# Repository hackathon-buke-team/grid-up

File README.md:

# PANO GÖZ / Son 7 takım arasına kalındı. Nihai sıralama açıklanmadı.

**Pano/hücre içi anomali erken uyarı sistemi — ADM & GDZ Elektrik "Grid Up" Hackathon**

Varlık: TEDAŞ-MLZ/2003-06.B, EK-II/14 çizimli, 1600 kVA dahili tip AG dağıtım panosu.
1600×1500×450 mm, 2312 A ana bara, 38 kA rms / 80 kA tepe kısa devre, IP2X, Form 2B.

---

## 1. Tez — bir paragrafta

Her yarışmacı panoya bir termometre koyar ve bir eşiğin üstünde alarm üretir. Bu sahada
çalışmaz: bir bağlantının sıcaklığını **durumu değil, yükü ve mevsimi** belirler. Şubatta
09:00'da 62 °C okunan bir pabuç kusurludur; ağustosta 15:00'te tam yükte okunan aynı 62 °C
normaldir. Sabit eşik ağustosu atlatacak kadar yükseğe kurulmak zorundadır, dolayısıyla
şubatta kördür. PANO GÖZ bunun yerine **θ**'yı ölçer:

```
θ_i = [ T_i − medyan(T_kardeşler) ] / (I / I_ref)²        [anma akımında kelvin]
```

Yük bölünerek düşer (I² sadeleşir), ortam sıcaklığı / mevsim / güneş kazancı çıkarılarak
düşer (aynı havadaki, 20 mm aralıklı, aynı yaştaki üç iletken), IR dizisinde yayıcılık
sadeleşir (aynı yüzey, aynı açı, aynı piksel dizisi). **Mutlak θ'nın kendisi geçmiş
gerektirmez**: bir bara üzerindeki üç özdeş faz, montaj gününde geçerli bir referanstır ve
ilk okumada doğrudan kullanılabilir. Bunun **kapsamı buraya kadardır**. Ürünün haftalar önce
haber veren yolu — kendi taban çizgisine göre yükselme, CUSUM teyidi, değişim noktası ve
3/5 günlük debounce — günlük medyanlar üzerinde çalışır ve **geçmiş gerektirir**: `joint_daily`
tablosunda en az beş gün olmadan sürüklenme teyit edilemez, kaynağından kurulan bir sistem o
beş günü beklemek zorundadır. Aynı tablodan **ileriye** bakan yol — bir sonraki seviye
basamağına kalan gün — daha fazlasını ister: 21 günlük pencerede en az **14 geçerli gün**
olmadan bir gün sayısı verilmez, `YETERSIZ_GECMIS` yazılır. İki yol birlikte satılır; "geçmiş gerektirmez" cümlesi yalnız
kardeş karşılaştırması için doğrudur. θ yeni bir icat değildir;
IR termografi pratiğinin zaten şart koştuğu "benzer bileşene göre benzer yük altında ΔT"
ölçütünün, yılda bir kez bir müteahhit tarafından değil, dakikada bir sürekli hesaplanan
hâlidir.

Sistem koruma yapmaz. Ark açması ABB TVOC-2 donanımında ~1 ms'de, SIL-2 seviyesinde
gerçekleşir ve bizi beklemez. Biz **gözlemler, konumlandırır, zaman damgalar, ilişkilendirir
ve yükseltiriz**.

---

## 2. Tek komutla çalıştırma

```powershell
# Windows PowerShell, proje kökünde
.\baslat.ps1
```

```bash
# ya da doğrudan
python -m panogoz.run_local
```

Docker gerekmez, broker kurulumu gerekmez, internet gerekmez. Varsayılan taşıma katmanı
süreç-içi bus'tır (`PANOGOZ_BUS=inproc`); gerçek Mosquitto'ya geçiş tek ortam değişkenidir
(`PANOGOZ_BUS=mqtt://host:1883`). Veri tabanının **tek sürücüsü vardır ve SQLite'tır**;
`PANOGOZ_DB` bir `postgresql://` adresi verildiğinde sessizce geri düşmez, hata verir.
TimescaleDB hedeflenen üretim yoludur ve **yazılmamıştır**: `schema.sql` taşınabilir SQL
olarak yazıldığı için PostgreSQL üzerinde değişmeden koşar, fakat hipertablo/sıkıştırma
cümleleri, toplu `COPY` yazma yolu ve Timescale üzerinde ölçüm yoktur.

Açılan uçlar:

| Uç | Adres | Ne için |
|---|---|---|
| Web arayüzü | http://127.0.0.1:8080/ | Dijital ikiz, alarm konsolu, bastırma ekranı |
| REST | http://127.0.0.1:8080/api/panel/SOKE-14 | Canlı pano görüntüsü (JSON) |
| WebSocket | ws://127.0.0.1:8080/ws | 1 Hz canlı akış |
| Sahte veri kanıtı | http://127.0.0.1:8080/api/analysis/supplied-data | §6'daki altı testin JSON hâli |
| SCADA southbound | Modbus TCP 127.0.0.1:5020 | Salt okunur register haritası |

Sık kullanılan seçenekler:

```
python -m panogoz.run_local --panels 112 --port 8080 --scada-port 5020 --backfill-days 75 --open
python -m panogoz.run_local --reset            # veritabanını silerek baştan
.\baslat.ps1 -Panels 24 -Port 8099            # daha küçük ve hızlı bir demo
```

### SCADA'yı kendiniz doğrulayın

```
modpoll -m tcp -0 -r 0    -c 20 -p 5020 127.0.0.1     # global blok
modpoll -m tcp -0 -r 1624 -c 48 -p 5020 127.0.0.1     # 14 numaralı pano bloğu
modpoll -m tcp -0 -r 1624 -p 5020 127.0.0.1 1         # yazma denemesi → exception 0x01
```

14 numaralı panonun adresi kafadan atılmadı: `PANEL_BASE + REGS_PER_PANEL × (n−1)`
= `1000 + 48 × 13` = **1624**. Yazma denemesi `ILLEGAL_FUNCTION` ile reddedilir — harita
istisnasız salt okunurdur (gerekçesi: [docs/PANOGOZ-ICD-v2.0.md](docs/PANOGOZ-ICD-v2.0.md)).

---

## 3. Jüri neye önce baksın

Beş dakikanız varsa sırayla şunlar:

1. **[docs/08-DEMO-SENARYOSU.md](docs/08-DEMO-SENARYOSU.md)** — ekranda ne olduğu, dakika dakika.
2. **Bastırılmış alarmlar ekranı.** Ürünün en ikna edici parçası ürettiğimiz alarmlar değil,
   **üretmediğimiz** alarmların gerekçeli listesidir. "78 °C okudun, neden bana söylemedin?"
   sorusunun cevabı ekranda, operatörün dilinde, sayılarıyla durur.
3. **Ark olayı beat'i.** TVOC-2 açar, biz açmayız; ekranda "koruma bizde değil" yazar ve
   bildirim gecikmesi tek bir temiz sayı olarak değil, **4–13 s aralığı** olarak gösterilir.
4. **[docs/04-ANOMALI-TESPIT.md](docs/04-ANOMALI-TESPIT.md) §3, görülebilirlik tablosu** —
   yük düştükçe kör olduğumuzu söyleyen tablo. Bunu saklamıyoruz, ekranda gösteriyoruz.
5. **Sağlanan verinin sentetik olduğu ve neyi ölçemediği** — altı istatistiksel ölçüm, §6.

Kod tarafında tek dosya okunacaksa: `panogoz/detector/theta.py`. Yöntemin tamamı ve neden
dekonvolüsyon yapmadığımız orada, ölçülmüş sayılarla yazılıdır.

---

## 4. Belge haritası

| Belge | İçerik |
|---|---|
| [docs/01-SISTEM-MIMARISI.md](docs/01-SISTEM-MIMARISI.md) | Uçtan uca mimari, "modül" tanımı, on-premise duruş, depolama aritmetiği, Sparkplug B reddi |
| [docs/02-DONANIM-TASARIMI.md](docs/02-DONANIM-TASARIMI.md) | 9 cihazlık kit, montaj yüzeyleri ve bunları sağlayan TEDAŞ maddeleri, çevresel tasarım, manyetik ortam |
| [docs/03-ELEKTRONIK-DOKUMANTASYON.md](docs/03-ELEKTRONIK-DOKUMANTASYON.md) | Kart blok şemaları, I/O tabloları, konnektör pin dizilimleri, katman yığını, HFCT analog zinciri, güç ağacı, BOM |
| [docs/04-ANOMALI-TESPIT.md](docs/04-ANOMALI-TESPIT.md) | θ türetimi, RLS kestirici, görülebilirlik tabanı, CUSUM/ARL0, yedi arıza modu, H3, yoğuşma, reddettiğimiz yöntemler |
| [docs/05-SAHA-UYGULAMA.md](docs/05-SAHA-UYGULAMA.md) | Kurulum prosedürü (yalnız Profil B), dizüstüsüz devreye alma, filo işletimi, TEDAŞ Madde 3.1 uyum notu |
| [docs/06-OLCEKLENEBILIRLIK.md](docs/06-OLCEKLENEBILIRLIK.md) | 100 → 1000 → 10 000 pano, ölçülmüş kaynak profili, RS-485 topolojisi |
| [docs/07-MALIYET-FAYDA.md](docs/07-MALIYET-FAYDA.md) | BOM maliyeti, 5 yıllık TCO, fayda modeli, **negatif senaryo önce** |
| [docs/08-DEMO-SENARYOSU.md](docs/08-DEMO-SENARYOSU.md) | 5 dakikalık demo, replikleriyle ve kesme çizgileriyle |
| [docs/09-VERI-ANALIZI.md](docs/09-VERI-ANALIZI.md) | Sağlanan `İstenen Veriler.xlsx` dosyasının tam karakterizasyonu — §6'daki kanıtların uzun hâli |
| [docs/10-MV-HUCRE-KONSEPTI.md](docs/10-MV-HUCRE-KONSEPTI.md) | OG hücre konsepti — çizim verilmedi, dürüstçe konsept |
| [docs/11-ACIK-SORULAR.md](docs/11-ACIK-SORULAR.md) | Yalnız müşterinin cevaplayabileceği sorular ve her birinin tasarımı nasıl değiştireceği |
| [docs/PANOGOZ-ICD-v2.0.md](docs/PANOGOZ-ICD-v2.0.md) | SCADA arayüz kontrol dokümanı — koddan üretilir, elle yazılmaz |
| [docs/panogoz_points.csv](docs/panogoz_points.csv) | Aynı haritanın SCADA import'u için düz nokta listesi |
| [sunum/PANO-GOZ-Final-Sunumu.pdf](sunum/PANO-GOZ-Final-Sunumu.pdf) | Final sunumu, PDF: 23 slayt, 16:9, yer imli |
| [sunum/index.html](sunum/index.html) | Aynı sunumun canlı hâli: tek dosya, internetsiz; N konuşma metni, S konuşmacı ekranı, Q jüri soruları. `python sunum/build.py --pdf` ikisini birlikte yeniden üretir |
| [sunum/SUNUM-METNI.md](sunum/SUNUM-METNI.md) | Sunucu için hazırlık kılavuzu: şartname ve bize verilen veriler, çözüm ve teknoloji yığını, slayt slayt konuşma metni, doğrulanmış canlı demo akışı, jüri soruları, ezber kartı |

---

## 5. Depo haritası

```
panogoz/
  contracts/      Tek doğruluk kaynağı — başka hiçbir yerde sayı tanımlanmaz
    assets.py       Pano geometrisi, 12 fider, 74 cıvatalı bağlantı, 9 cihaz, kardeş grupları
    channels.py     Kanal (metrik) kütüğü, 7 arıza modu ve ağırlıkları, 5 kademeli seviye merdiveni
    envelope.py     Telemetri zarfı, MQTT konu şeması, sıra numarası takibi
    icd.py          SCADA Modbus register haritası (ICD belgesi buradan üretilir)
    live.py         PanelLive / JointView / ArcView / PdView — ekran ile register aynı nesneden
  store/          SQLite (tek sürücü) + taşınabilir şema (store/schema.sql)
  bus/            Süreç-içi ve MQTT sürücüleri, aynı arayüz
  sim/            Dijital ikiz: yük, ısıl model, 17 arıza senaryosu, TVOC-2 ve MPR-53CS
                  register sunucuları, PRPD üreteci
  gateway/        Modbus master (poller), ağ geçidi, yerel kritik kurallar, store-and-forward
  detector/       θ (RLS), CUSUM, değişim noktası, çiy noktası, nötr H3, motor
  rules/          Bastırma → füzyon → alarm yaşam döngüsü
  notify/         GSM modem / SMPP, vardiya merdiveni, onay jetonu
  scada/          Modbus TCP slave (salt okunur) ve ICD üreteci
  api/            REST + WebSocket + demo senaryo uçları
  run_local.py    Tek süreçte tüm sistem — ana çalıştırma yolu
baslat.ps1        Windows tek komut sarmalayıcısı (ağa çıkmaz, paket kurmaz)
firmware/node/    Uç düğüm firmware'i, C99, STM32WLE5CC, float yok, malloc yok
frontend/         Arayüz: dijital ikiz, alarm konsolu, bastırma ekranı, SCADA görünümü
analysis/         Sağlanan xlsx dosyasının istatistiksel karakterizasyonu
tests/            Kabul testleri; her modülün ayrıca kendi self-test'i var
docs/             Bu belge paketi
```

Her modül tek başına çalışır ve kanıt basar:

```
PYTHONIOENCODING=utf-8 python -m panogoz.detector.theta      # θ kestiricisi, RLS vs dekonvolüsyon
PYTHONIOENCODING=utf-8 python -m panogoz.detector.cusum      # ARL0 aritmetiği ve otokorelasyon cezası
PYTHONIOENCODING=utf-8 python -m tests.test_integration      # uçtan uca kabul kapısı
PYTHONIOENCODING=utf-8 python -m tests.test_scada            # 100 panolu Modbus taraması
PYTHONIOENCODING=utf-8 python -m analysis.supplied_data      # sağlanan kümenin analizi
PYTHONIOENCODING=utf-8 python -m pytest -q                   # gerileme takımı (regression)
```

Gerileme takımı, daha önce gerçekten yaşanmış hataları yeniden üretip kilitler:

| Dosya | Neyi kilitler |
|---|---|
| `tests/test_alarm_load_regression.py` | Dedektör kararının anlık θ ile ezilmemesi; bara/fider yük ölçeklerinin ayrı kalması; geçmişten debounce penceresi kurulabilmesi |
| `tests/test_transport_regression.py` | Paho `ReasonCode` işlenmesi; PUBACK'sız mesajın tampondan düşmemesi; yeniden başlatmada outbox'ın geri yüklenmesi |
| `tests/test_stream_regression.py` | Tekrarlanan/eski zarfın canlı değeri, RLS'yi ve tazelik saatini geri almaması |
| `tests/test_cadence_regression.py` | Tazelik pencerelerinin cihazın ilan ettiği periyottan türetilmesi (900/60/10 s) |
| `tests/test_thd_attribution_regression.py` | Üç faz THD'sinin şebeke olayı **adayı** sayılması; ısıl bulguyu tek başına silmemesi |
| `tests/test_negative_pipeline.py` | Yedi negatif kontrolün gerçek boru hattında alarm üretmemesi — ve aynı koşumda pozitif kontrolün üretmesi |

---

## 6. Sağlanan veri hakkında — sentetiktir, bu yüzden saha başarısı bununla ölçülemez

Yarışma verisi örnek/sentetik bir kümedir; bunu ortaya çıkarmak bir başarı değildir,
**sonuçlarını dikkate almak** bir zorunluluktur. Aşağıdaki ölçümler "verinizi yakaladık"
demek için değil, bu kümeyle **neyin ölçülemeyeceğini** sayıyla göstermek için yapılmıştır.

Kümede olmayanlar, doğrudan bizim problemimiz oldukları için önemlidir:

* **Sıcaklık ve nem yok.** `Sıcaklık_Nem` sayfası tamamen boştur. θ bir sıcaklık farkıdır;
  sıcaklık serisi olmayan bir veri kümesinde θ hesaplanamaz, dolayısıyla bu dosya
  dedektörün doğruluğu hakkında hiçbir şey söyleyemez.
* **Etiketli arıza geçmişi yok.** Hangi bağlantının ne zaman gevşediği kayıtlı değildir;
  yanlış alarm oranı ya da haber verme süresi bu kümeden **hesaplanamaz**.
* **Kardeş yapısı yok.** Tek bir akım serisi vardır; θ'nın dayandığı üç faz / komşu pabuç
  eşleşmesi yoktur.
* **Anomali yok.** Küme panonun anmasının %3.9 ile %23.4'ü arasında yaşar: aşırı yük yok,
  tepe yok, olay yok.

"Akım Sensörü" sayfası 15 dakika aralıklı 152 satırdır ve düzgün dağılımlı gürültü
imzası taşır (`=RASTGELEARADA(15;90)` ile uyumlu). Altı bağımsız ölçüm:

| Test | Ölçülen | Gerçek bir fiderde beklenen |
|---|---:|---|
| Lag-1 otokorelasyon | +0.0003 | > +0.97 |
| var(fark)/var(seri) | 2.0023 | ≪ 2 (tam beyaz gürültü değeri 2) |
| Fazlalık basıklık | −1.2129 | ≈ 0 (−1.2 kesikli düzgün dağılım imzasıdır) |
| KS testi, U(14.5, 90.5) | D = 0.0526 | 0.1101 kritik değerini aşmalı |
| 76 tam sayı üzerinde χ² düzgünlük | χ² = 76.00, sd = 75, p = 0.446 | reddedilmeli |
| Aynı saatte gün-üstü şekil korelasyonu | r = +0.0596 | > 0.85 |

Saatlik ANOVA da farksızdır: F(23,128) = 1.375, p = 0.135 — gerçek bir fiderde günün saati
akımı belirler. Ham istatistikler: n = 152, min 15, maks 90, ortalama 52.1316, medyan 49.5,
sd 22.6504, CV 0.4345 mA; ×6 ile primer 90…540 A, ortalama 312.79 A.

Ek olarak sayfanın kendi başlığı çelişkilidir: "125 mA karşılığı 5 A" bir 40:1 ara akım
trafosunu tarif eder, TEDAŞ 2500/5 ile kaskat 20 000:1 = 20.0 A/mA eder; oysa formül
`600000/100` = 6000 = **6.0 A/mA** uygular. Aradaki fark 3.33 kattır. Üstelik
125 mA × 6.0 = 750 A'dir, belirtilen 600 A tam ölçek değil.

Bu yüzden model eğitimini sağlanan veriye dayandırmadık. Fizikten türetilmiş bir dijital
ikiz kurduk (`panogoz/sim/`), kabul kriterlerini ölçtük (`tests/test_sim_acceptance.py`) ve
sağlanan kümeyi de aynı testlerden geçirdik. Bunun sonucu şudur ve açıkça söylenmelidir:
**bu paketteki hiçbir başarım sayısı saha verisiyle doğrulanmış değildir.** Hepsi ya
fizikten türetilmiş bir simülatör üzerinde, ya da analitik olarak (CUSUM ARL formülü,
θ_min = 3σ/f²) hesaplanmıştır. Gerçek yanlış alarm oranı ancak etiketli saha geçmişi olan
bir pilot tesiste ölçülebilir.

---

## 7. Yapmadıklarımız ve nedenleri

Bir hackathon teslimi için en değerli bölüm budur.

| Yapmadık | Neden |
|---|---|
| **Bara bölmesine sensör** | Panoda AG giriş kesicisi **yoktur** ("direk bara bağlantı", Madde 2.2.10.2.vi). Bara bölmesini enerjisiz yapmak, tüm dağıtım merkezini OG tarafından karartmak demektir. 1. gün kiti yalnız alt kablo bölmesi + ölçü kolonu + mevcut 10 A prizdir. Bara bölmesi profilini yazmadık, **sildik**. |
| **Enerji hasadı iddiası** | Bara yakınında akım trafosuyla hasat teorik olarak mümkündür; ölçmedik. Ölçmediğimiz bir şeyi teklif etmeyiz. Birincil Li-SOCl2 hücre, 9–16 yıl tasarım ömrü. Hasat, tezgâh ölçümüne bağlı belgelenmiş bir gelecek seçeneği olarak durur. |
| **Tek başına PD ile ekip yönlendirme** | 400 V'ta klasik kısmi deşarj oluşmaz (Paschen minimumu 327 V). RF kanalı gevşek bağlantı mikro-arkını ölçer, pC **eşdeğeri** raporlar, IEC 60270 izlenebilir **değildir** ve AG'de tek başına asla ekip yönlendirmez — yalnız ısıl bulguyu destekler. |
| **Derin öğrenme / pano başına LSTM** | Kayan pencerede eğitilen bir otokodlayıcı yavaş sürüklenmeyi **öğrenir ve yeniden üretir**; yani tam olarak avladığımız 0.2 K/hafta sinyaline yapısal olarak kördür. Ayrıca elimizde olmayan aylarca temiz geçmiş ister ve 100 panoya özel 100 model bir işletme yüküdür. Gerekçeler: [docs/04](docs/04-ANOMALI-TESPIT.md) §10. |
| **SCADA'ya yazma yolu** | Modbus'ta kimlik doğrulama yoktur. TVOC-2'ye otokontrol komutu verebilen bir sisteme kimliksiz yazma açmak kabul edilemez. FC 05/06/15/16 istisnasız reddedilir. |
| **Sparkplug B** | Sparkplug 3.0, DDATA için QoS 0 **zorunlu** kılar. Dayanıklılık hikâyemiz ağ geçidinde PUBACK ile ilerleyen bir store-and-forward filigranına dayanır ve bu mekanizma QoS 0'da yoktur. Doğum/vasiyet/monoton sıra numarasını koruduk, markayı bıraktık. |
| **IEC 60870-5-104 ve OPC UA sunucuları** | Nokta listeleri yazıldı, sunucular kurulmadı. Bu hackathonda **yalnız Modbus TCP slave çalışır durumda** teslim edilmiştir. |
| **Gerçek SMS gönderimi** | GSM modem AT diyaloğu ve SMPP oturumu gerçekçi biçimde simüle edilir, transkript kaydedilir; hiçbir yere mesaj gitmez. Sesli arama yolu da simülasyondur; gerçek dağıtım TTS ağ geçidi ister. |
| **KiCad kaynak dosyaları** | Kart tasarımı blok şema, I/O tablosu, konnektör pin dizilimi, katman yığını ve BOM düzeyinde belgelenmiştir. Saklanan bir dosya yoktur; **çizilmemiştir**. |
| **OG hücre donanımı** | Hiçbir OG çizimi verilmedi; istedik. [docs/10](docs/10-MV-HUCRE-KONSEPTI.md) jenerik 36 kV kablo bölmesi için konsept, montaj ve maliyet verir, ürün iddia etmez. |

---

## 8. Dürüstlük kuralları

Bunlar pazarlama cümlesi değil, kodda karşılığı olan kurallardır.

1. **PANO GÖZ koruma değildir.** Bildirim gecikmesi bir aralıktır: TVOC-2 Modbus görüntüsünün
   yenilenmesi (ABB dokümante etmiyor, 0.2–2 s modellendi) + 1 s tarama + sunucu + SMS yolu
   = **4–13 s**. Tek temiz sayı vermiyoruz.
2. **Kör olduğumuz yeri söyleriz.** `DE_ENERGISED`, `SENSITIVITY_LOW`, `MOUNT_LOST`,
   `AIM_SHIFTED`, `CELL_LOW`, `STALE` birinci sınıf durumlardır; pano arızalarından ayrı
   raporlanır, asla karıştırılmaz.
3. **Bastırılmış alarmlar kendi ekranı ve kendi gerekçesi olan bir üründür.**
4. **Enerji hasadı iddia edilmez.**
5. **Enerjili bara bölmesine montaj iddia edilmez.**

---

## 9. Belgelendi, kodlanmadı

Bu paketin her belgesinin sonunda aynı başlıkla bir liste vardır. Kısa özet:

| Konu | Durum |
|---|---|
| IEC 60870-5-104 / OPC UA sunucuları | Nokta listesi var, sunucu yok |
| KiCad şematik ve PCB kaynağı | Blok/I-O/BOM düzeyinde belgelendi, çizilmedi |
| Gerçek GSM/SMPP gönderimi, sesli arama | Simüle edildi, transkript üretiliyor |
| OTA imzalı firmware dağıtımı | Politika yazıldı, dağıtım altyapısı kurulmadı |
| TimescaleDB sürücüsü | **Yok.** `Store` yalnız SQLite'tır; `postgresql://` adresi reddedilir |
| TimescaleDB hipertablo/sıkıştırma/sürekli toplam cümleleri | **Yazılmadı.** `schema_timescale.sql` diye bir dosya yoktur |
| Timescale toplu `COPY` yazma yolu | Yok; belgelerdeki Timescale rakamları yayınlanmış veriden türetilmiştir, ölçüm değildir |
| `docker-compose.yml` güvenlik seviyesi | Topoloji tarifidir, sertleştirme değildir: çalışan dinleyici anonim düz MQTT, mTLS ve ACL yorum satırında, host portları doğrudan yayında |
| Enerji hasadı | Ölçülmedi, iddia edilmiyor |
| OG hücre donanımı | Konsept, prototip yok |
| NFC ile devreye alma | Akış tasarlandı, NFC yongası tezgâhta denenmedi |
| "Eşiğe kalan gün" için SCADA register'ı | **Yok.** 48 register'lık pano bloğu tam dolu; büyütmek her panonun taban adresini kaydırır ve yayınlanmış ICD v2.0'ı bozar. Eklemeli bir ETA bloğu [docs/04](docs/04-ANOMALI-TESPIT.md) §6.1.5'te tarif edildi, kurulmadı |
| Ufuk projeksiyonunun saha kalibrasyonu | Güven aralığının kapsaması **simülasyonda** ölçüldü (nominal %90'a karşı %88-93). Gerçek haber verme süresi ancak etiketli saha geçmişiyle ölçülebilir |

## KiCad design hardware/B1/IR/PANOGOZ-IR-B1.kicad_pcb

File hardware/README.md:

# K1 / B1 tasarım teslimi

20.09.2026. `k1-b1-tasarim-firmware` dalı; başlangıç: `74490f50`.
Bu klasör repodaki STM32/LoRa mimarisine göre oluşturulmuştur. Önceki bağımsız ESP32 RevA paketi bu teslimin kaynağı değildir.

## Önce açılacak dosyalar

- [Tasarım ve ölçülendirilmiş montaj dosyası](B1/K1-B1-TASARIM-DOSYASI.pdf): verilen 1600 kVA çizimi üzerinde montaj, kutular, kablo yolları ve sınırlar.
- [TC şematiği](B1/TC/schematic.pdf), [IR şematiği](B1/IR/schematic.pdf), [PD şematiği](B1/PD/schematic.pdf), [GW şematiği](B1/GW/schematic.pdf).
- [BOM ve güncel fiyat kaynakları](B1/BOM.md), [satır bazında teklif/alternatif/termin](B1/bom.json).
- [Doğrulama raporları](B1/verification.json), [firmware hedef portu](../firmware/node/port/stm32wle5/README.md).

Her `B1/TC`, `IR`, `PD`, `GW` klasöründeki `PANOGOZ-*-B1.kicad_pro` dosyası **KiCad 10** ile açılır. Şematik sayfaları, PCB, yerel semboller, modeller, `pinmap.csv`, `circuit.json`, `pcb-top.png`, `pcb-bottom.png`, `pcb-3d.png` aynı dizindedir. `mechanical/*/assembly.step`, `base.step`, `lid.step` STEP uyumlu CAD yazılımlarında düzenlenebilir; parametrik kaynak `tools/mechanical.py` dosyasıdır.

## Kabul matrisi

| K1 | Yapılan / kanıt | Durum |
|---|---|---|
| 1.1 | Dört fiziksel kartın elektriksel bağlantılı şematiği; PDF; ERC 0 hata/0 uyarı; BOM/pinmap manifestten üretilir | Tasarım aşaması tamam |
| 1.2 | Boyut, dört katman, konnektörler, keepout, üst/alt/3B PNG; yerleşim DRC 0; şematik-PCB farkı 0 | Yerleşim tamam; bakır yönlendirme yapılmadı |
| 1.3 | Orijinal pano çizimi üstüne montaj, ölçülü ön görünüş, derinlik kademesi, kablo/erişim, kutu STEP dosyaları | Konsept çizimleri tamam; saha ölçümü yapılmadı |
| 1.4 | Gerçek Cortex-M4 ELF/BIN/MAP; ST HAL/CMSIS; uyarısız derleme ve host öz testi | TC hedefi tamam; fiziksel çalıştırma yok |
| 1.5 | Çevre/koruma önlemlerinin bileşen ve yerleşim karşılıkları docs/03 içinde | Tasarım karşılıkları yazılı; test/sertifika yok |
| 1.6 | 214 BOM satırı; 15 parça tipinin 19 satırda gözlenen USD fiyatları; ref bazlı tedarik açıkları ve yeniden üretilen maliyet hesabı | **Kısmen**: 195 satırda fiyat eksik; kesin MPN/teslim teyitleri açık |
| 1.7 | İsteğe bağlı gerçek sensör demosu | Donanım satın alınmadı; uygulanmadı |

Görev belgesi “TC, IR/PD, GW” olarak üç işlev grubu sayar. Mevcut repo IR ve PD'yi iki farklı pil düğümü olarak tanımlar; bu nedenle dört kart tipi, **6 TC + 1 IR + 1 PD + 1 GW = 9 cihaz** korunur. `panogoz/contracts/` değişmedi. K1 uyum düzeltmesi; gateway'de kalıcı düğüm kabulü, simülasyonda B1 optik/pil sınırları, API/arayüzde kapsam ve ölçümsüz bağlantının tahmin gerekçesini kapsar. Bu ortak dosyalar ekip birleştirmesinde gözden geçirilmelidir.

## B1 yazılım uyumu

Varsayılan dijital ikiz 6 TC noktasından bağımsız sıcaklık/akım üretir. 38 mm/piksel ve 20 mm pabuç adımı nedeniyle kalibre edilmiş tekil IR ROI listesi boştur; 34 diğer nokta için sahte IR sıcaklığı verilmez. Fizik modeli 40 bağlantının gerçeğini ayrı tutar. `ideal_ir=True` yalnız açıkça seçilen çevrimdışı sensör deneyidir; çalışan filo bunu kullanmaz. Eski pil ve geri ödeme iddiaları kaldırılmıştır. Radyo zarfı kalıcı gateway kuyruğuna bağlanmıştır; fiziksel alıcı sürücüsü hâlâ açık iştir.

[Güncel maliyet](../docs/07-MALIYET-FAYDA.md), [tedarik açıkları](B1/TEDARIK-ACIKLARI.md), [maliyet çıktısı](B1/cost-summary.json). Eski demo veritabanı ideal IR geçmişi içerebilir; B1 demosu yeni bir `PANOGOZ_DB` dosyasıyla başlatılmalıdır, eski veri silinmez.

## Dijital ikizde K1 çizimleri

Pano ekranındaki bir cihaza veya **Kart ve kutu çizimlerini aç** düğmesine basın. TC-01–TC-06 aynı TC kartına; TN-IR, PD-01 ve GW-01 kendi B1 tasarımlarına bağlanır. Galeride mekanik kutu modeli, PCB 3B/üst/alt görünümleri, şematik PDF, STEP ve KiCad PCB bağlantıları bulunur. Pano montaj PDF'si de buradan açılır. Önizlemeler mevcut CAD çıktılarıdır; etkileşimli 3B döndürme yoktur, STEP dosyası CAD yazılımında açılabilir.

Pano çizimindeki cihaz kutuları `mechanical/dimensions.json` nominal ölçülerini kullanır. İçlerindeki izometrik görsel ön görünüş ölçülendirmesi değildir; gerçek pano açıklıkları ve montaj hâlâ fiziksel doğrulama gerektirir. Canlı ölçümler ve bağlantı tıklamaları korunur.

Sunucu `/api/panel/{key}/twin` yanıtında cihaz–tasarım eşlemesini ve `design_catalog` alanını verir; `/api/hardware/B1/` yalnız 29 açıkça listelenmiş teslim dosyasını sunar. Başka donanım dosyaları servis edilmez. Ekip güncellemesinde API, arayüz ve `hardware/B1/` birlikte alınmalı ve sunucu yeniden başlatılmalıdır. Ek program kurulumu gerekmez.

## Testlerin anlamı

KiCad ERC elektriksel pin/ağ tutarlılığını kontrol eder; analog doğruluk, RF uyumu veya doğru firmware pin-mux seçimini tek başına kanıtlamaz. Pin-mux kontrolü üretici tablolarına göre ayrıca yapılmıştır. Yerleşim DRC ihlali 0 olmakla birlikte TC/IR/PD/GW için sırasıyla **167/162/253/396 yönlendirilmemiş bağlantı** vardır. Bu paket bir Gerber/üretim sürümü değildir. DRC bulguları gizlenmedi; raporların `unconnected_items` alanları teslim edilir.

Repo testleri ve host/ARM çıktıları `B1/evidence/` altında saklanır. B1 uyum güncellemesinin sonuçları [uyum doğrulamasında](B1/UYUM-DOGRULAMA.md) bulunur. Tam repo testi temiz değildir: sağlıklı bağlantıya 90 gün altında IZLE tarihi veren negatif kontrol hataları vardır; `trafo_devreye_alma` hatası değişmemiş ana sürümde de yeniden üretildi. Alarm/tahmin eşikleri ve negatif kontrol testleri değiştirilmedi. Ölçüm almayan bağlantıların boş tahmin gerekçesi düzeltildi. Önceki başarılı koşu bu açık hataları ortadan kaldırmaz.

## Üretim öncesi açık işler

RF eşleme değerleri başlangıç değerleridir; QFN/868 MHz için son PCB üzerinde VNA/iletim testi gerekir. Analog koruma, CT/HFCT transferi, pil/HLC tepe akımı, kutu sızdırmazlığı/mandalı, termal temas, IR piksel ayrımı ve gerçek pano açıklıkları ölçülmedi. IR/PD hedef sensör portları, H563 GW MCU yazılımı ve fiziksel radyo alıcısı henüz yok. Yazılım radyo zarfı → kalıcı gateway kuyruğu → QoS1/PUBACK yolu testlidir. TC hedefinde imzalı bootloader olmadığı için OTA kapalıdır.

## Yeniden üretim

```powershell
# KiCad Python; KICAD_SHARE gerekirse kurulum dizinine ayarlanır
& '<KiCad>/bin/python.exe' hardware/tools/generate.py
python hardware/tools/export.py # KICAD_CLI ile CLI yolu seçilebilir
python hardware/tools/bom.py
python hardware/tools/costs.py
# CadQuery 2.6 + matplotlib bulunan Python
python hardware/tools/mechanical.py
# ReportLab; fontlar Windows Arial
python hardware/tools/report.py
python firmware/node/build_target.py --toolchain '<ARM GCC>/bin' --node 4
python -m pytest -q
```

Model ve PDF dışa aktarımlarında KiCad'in normal kullanıcı önbelleğine yazabilmesi gerekir. İlk CAD üretiminden önce `mechanical.py` özel GW model zarflarını üretir; sonrasında `generate.py → export.py → bom.py → report.py` sırası kullanılır. Şematikteki fiziksel pinler kaynak manifestte tanımlıdır; elle CAD düzenlenecekse `generate.py` yeniden çalıştırmak bu düzenlemeleri üzerine yazar.

Standart sembol/ayak izi/3B modeller KiCad kütüphanelerinden alınmıştır (CC BY-SA 4.0 ve KiCad library exception); özel E22/TE geometrileri üretici ölçülerinden türetilmiş yaklaşık modellerdir. QFN gövde önizlemesinde 5,15 mm EP modeli kullanılabilir, elektriksel footprint EP ölçüsü 5,6 mm kalır. `model_report.json` eksik/temsili modelleri belirtir. ST/CMSIS yazılımlarının ayrı lisansları vendor dizininde korunur.

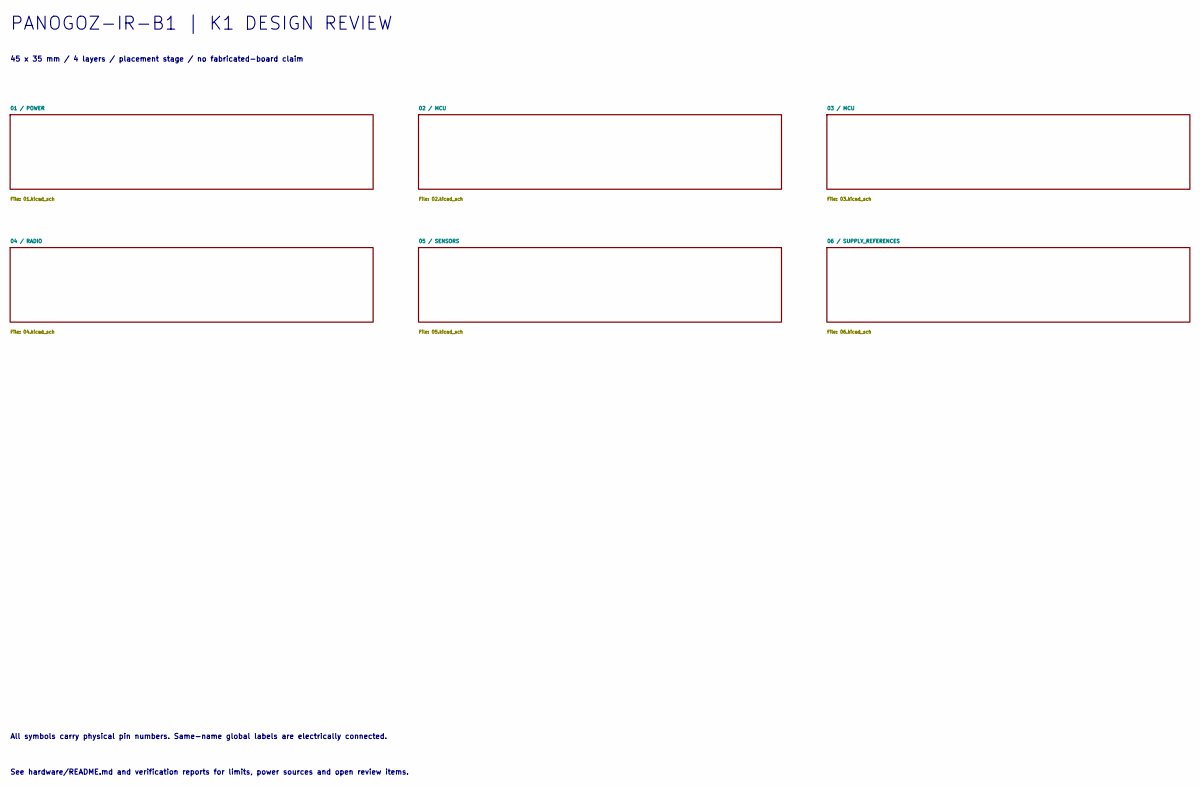
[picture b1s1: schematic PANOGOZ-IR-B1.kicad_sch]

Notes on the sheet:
PANOGOZ-IR-B1 | K1 DESIGN REVIEW
45 x 35 mm / 4 layers / placement stage / no fabricated-board claim
All symbols carry physical pin numbers. Same-name global labels are electrically connected.
See hardware/README.md and verification reports for limits, power sources and open review items.

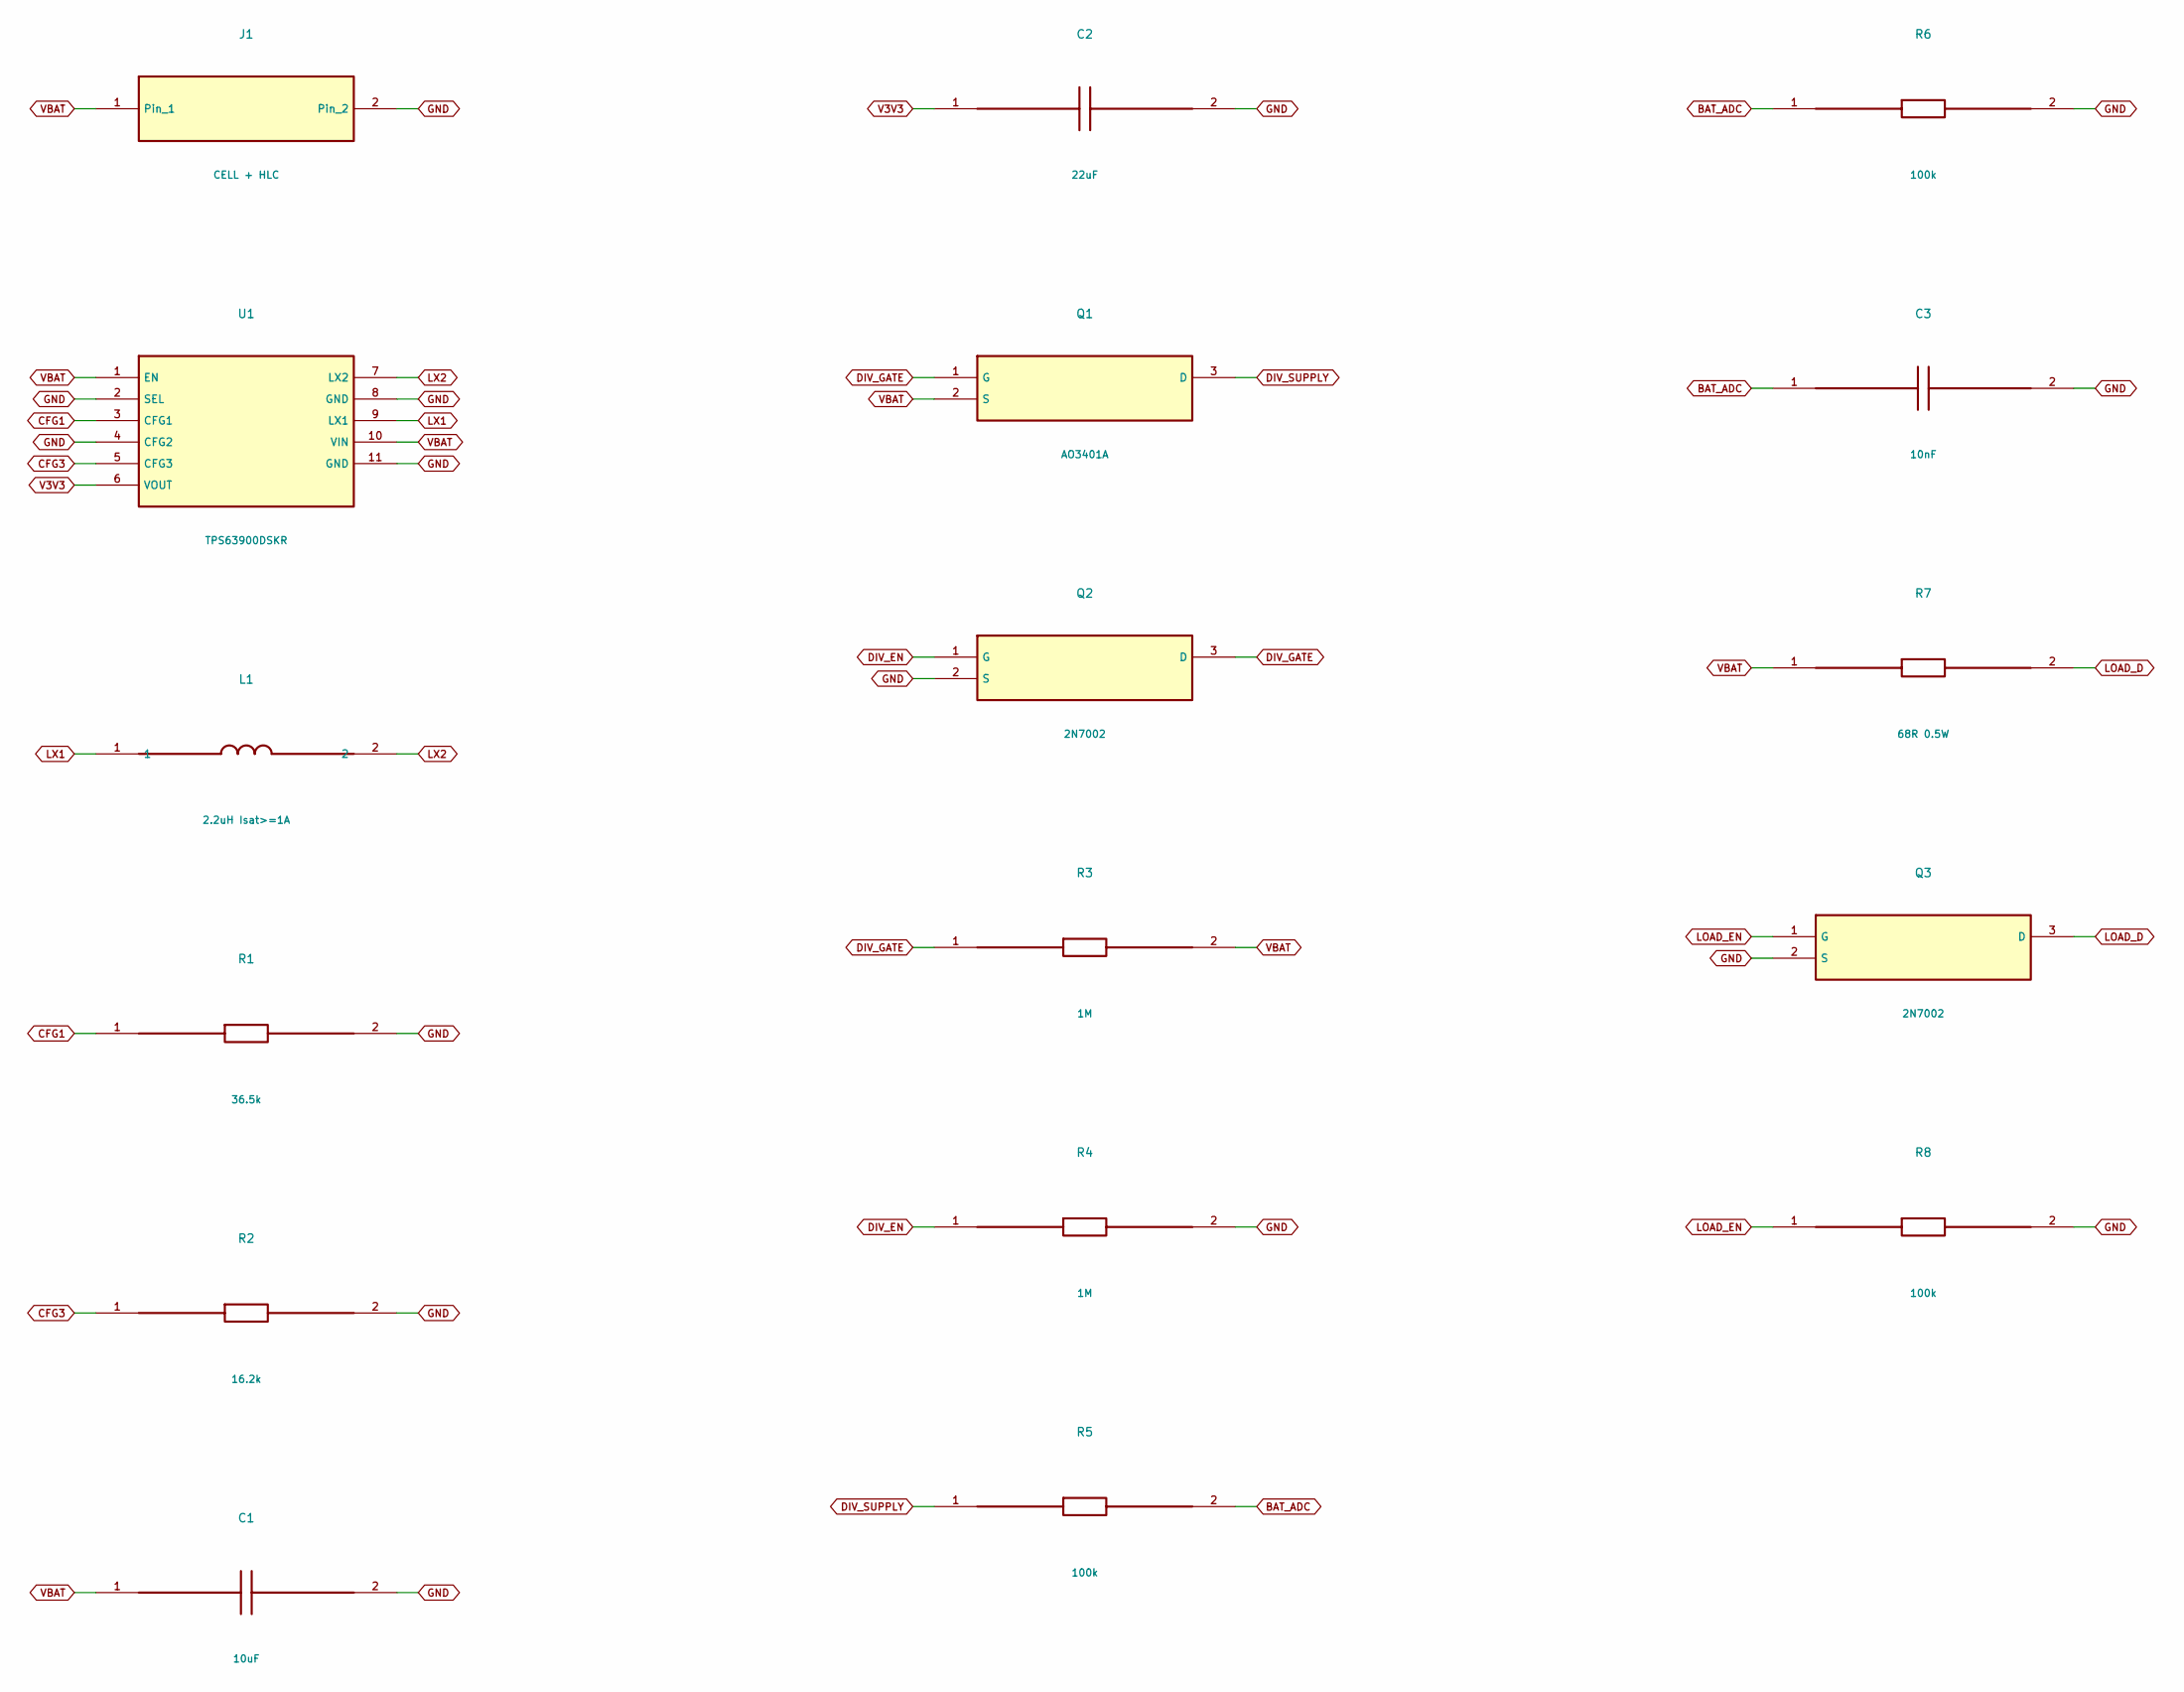
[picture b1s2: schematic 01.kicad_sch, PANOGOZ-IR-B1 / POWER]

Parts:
C1: 10uF; C_0805_2012Metric; MPN X7R 16V 10uF
C2: 22uF; C_0805_2012Metric; MPN X7R 16V 22uF
C3: 10nF; C_0402_1005Metric; MPN X7R 16V 10nF
J1: CELL + HLC; JST_SH_SM02B-SRSS-TB_1x02-1MP_P1.00mm_Horizontal; MPN CELL + HLC
L1: 2.2uH Isat>=1A; L_0805_2012Metric; MPN 2.2uH Isat>=1A
Q1: AO3401A; SOT-23; MPN AO3401A
Q2, Q3: 2N7002; SOT-23; MPN 2N7002
R1: 36.5k; R_0402_1005Metric; MPN 1% thick film 36.5k
R2: 16.2k; R_0402_1005Metric; MPN 1% thick film 16.2k
R3, R4: 1M; R_0402_1005Metric; MPN 1% thick film 1M
R5, R6, R8: 100k; R_0402_1005Metric; MPN 1% thick film 100k
R7: 68R 0.5W; R_1210_3225Metric; MPN 1% thick film 68R 0.5W
U1: TPS63900DSKR; WSON-10-1EP_2.5x2.5mm_P0.5mm_EP1.2x2mm_ThermalVias; MPN TPS63900DSKR

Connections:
BAT_ADC: C3.1, R5.2, R6.1; also elsewhere on the board
CFG1: R1.1, U1.3 (CFG1)
CFG3: R2.1, U1.5 (CFG3)
DIV_EN: Q2.1 (G), R4.1; also elsewhere on the board
DIV_GATE: Q1.1 (G), Q2.3 (D), R3.1
DIV_SUPPLY: Q1.3 (D), R5.1
GND: C1.2, C2.2, C3.2, J1.2, Q2.2 (S), Q3.2 (S), R1.2, R2.2, R4.2, R6.2, R8.2, U1.2 (SEL), U1.4 (CFG2), U1.8 (GND), U1.11 (GND); also elsewhere on the board
LOAD_D: Q3.3 (D), R7.2
LOAD_EN: Q3.1 (G), R8.1; also elsewhere on the board
LX1: L1.1, U1.9 (LX1)
LX2: L1.2, U1.7 (LX2)
V3V3: C2.1, U1.6 (VOUT); also elsewhere on the board
VBAT: C1.1, J1.1, Q1.2 (S), R3.2, R7.1, U1.1 (EN), U1.10 (VIN)

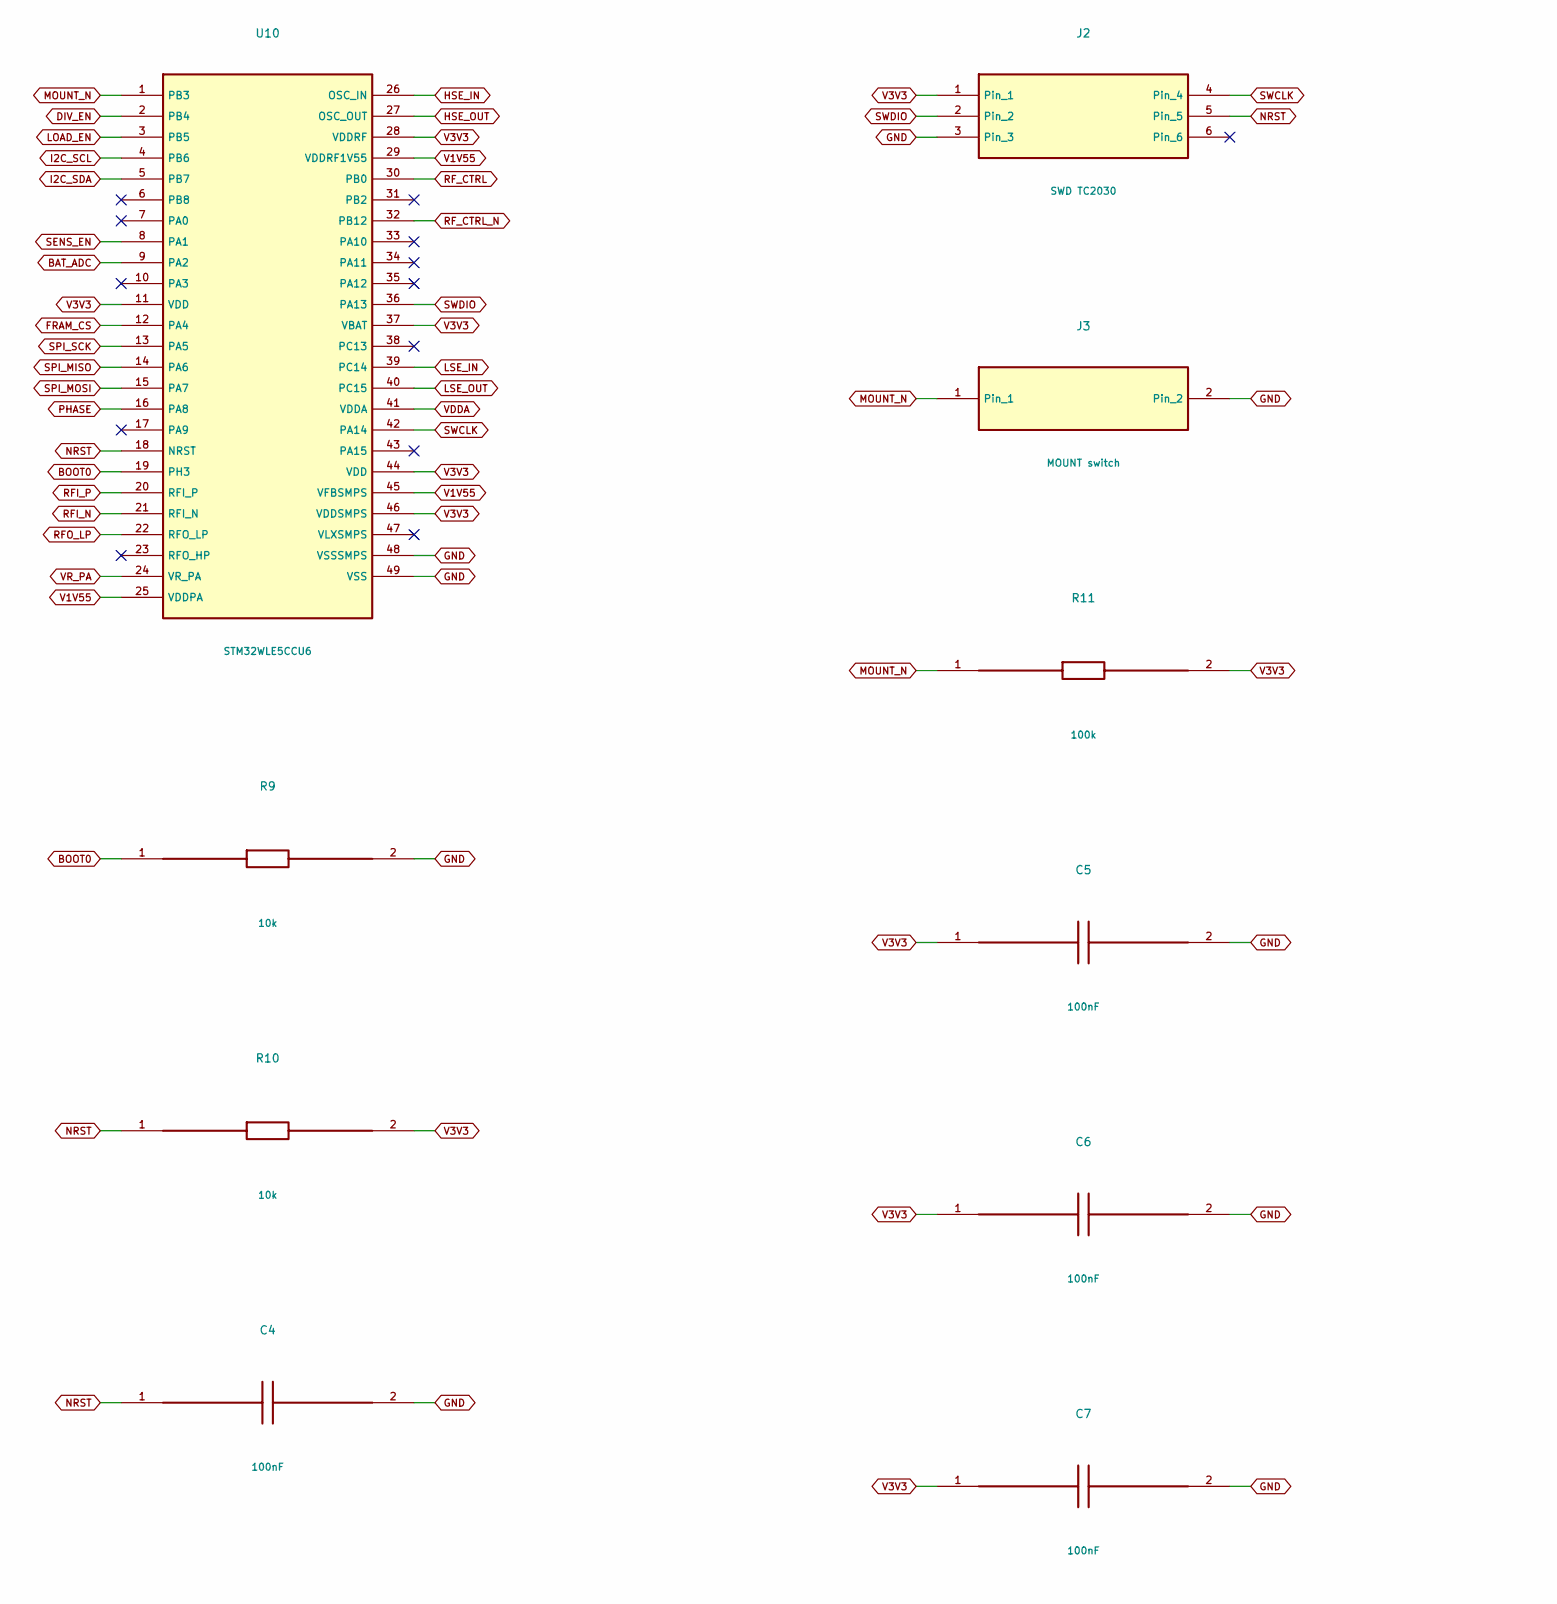
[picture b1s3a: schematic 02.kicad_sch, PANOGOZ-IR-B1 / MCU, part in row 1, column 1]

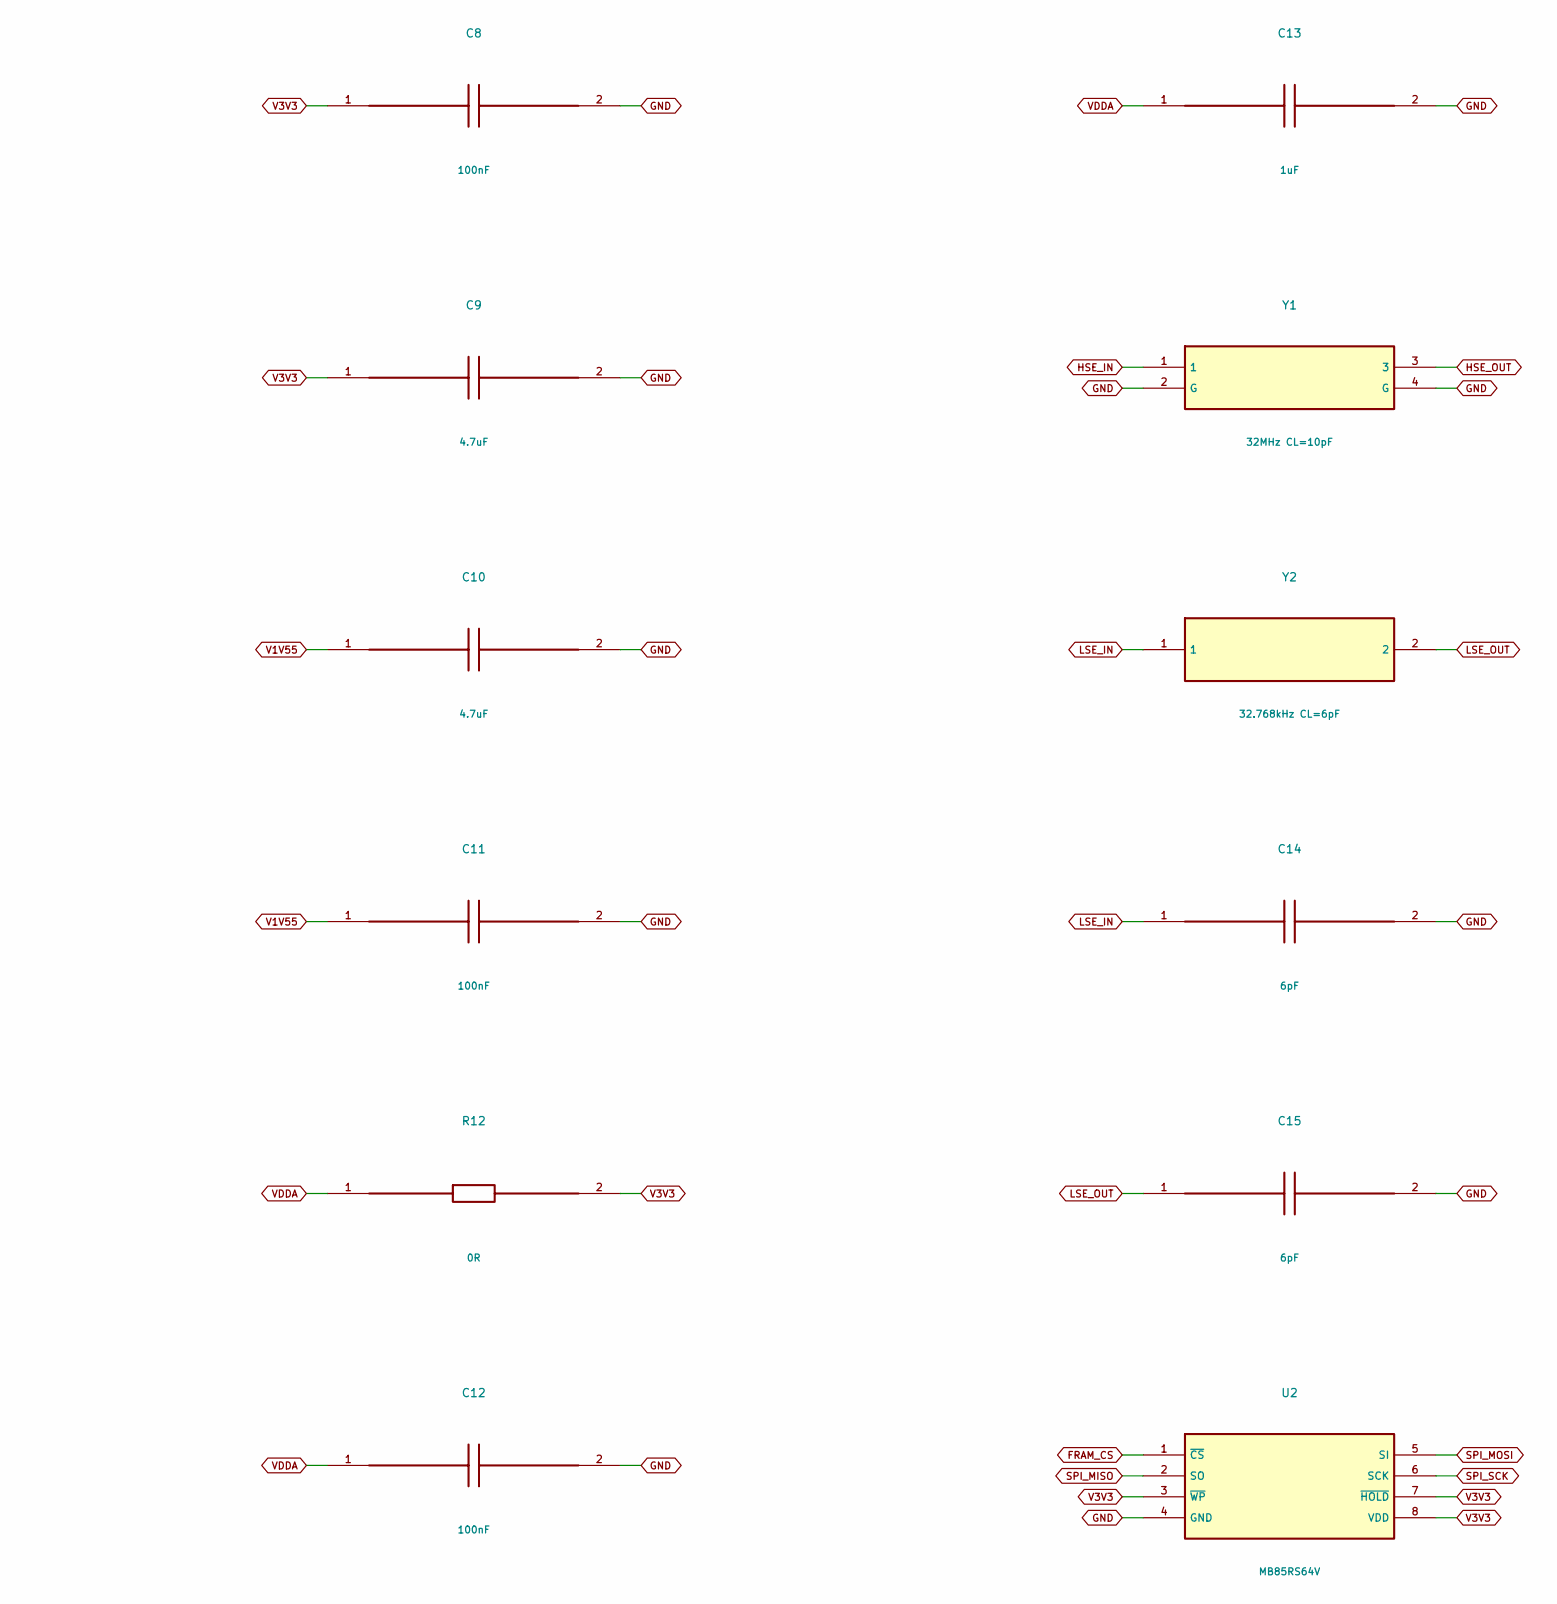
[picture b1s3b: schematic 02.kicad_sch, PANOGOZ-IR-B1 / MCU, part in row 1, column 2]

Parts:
C4, C5, C6, C7, C8, C11, C12: 100nF; C_0402_1005Metric; MPN X7R 16V 100nF
C9, C10: 4.7uF; C_0402_1005Metric; MPN X7R 16V 4.7uF
C13: 1uF; C_0402_1005Metric; MPN X7R 16V 1uF
C14, C15: 6pF; C_0402_1005Metric; MPN X7R 16V 6pF
J2: SWD TC2030; Tag-Connect_TC2030-IDC-NL_2x03_P1.27mm_Vertical; MPN SWD TC2030
J3: MOUNT switch; JST_SH_SM02B-SRSS-TB_1x02-1MP_P1.00mm_Horizontal; MPN MOUNT switch
R9, R10: 10k; R_0402_1005Metric; MPN 1% thick film 10k
R11: 100k; R_0402_1005Metric; MPN 1% thick film 100k
R12: 0R; R_0402_1005Metric; MPN 1% thick film 0R
U2: MB85RS64V; SOIC-8_3.9x4.9mm_P1.27mm; MPN MB85RS64V
U10: STM32WLE5CCU6; QFN-48-1EP_7x7mm_P0.5mm_EP5.6x5.6mm; MPN STM32WLE5CCU6
Y1: 32MHz CL=10pF; Crystal_SMD_3225-4Pin_3.2x2.5mm; MPN 32MHz CL=10pF
Y2: 32.768kHz CL=6pF; Crystal_SMD_3215-2Pin_3.2x1.5mm; MPN 32.768kHz CL=6pF

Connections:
BAT_ADC: U10.9 (PA2); also elsewhere on the board
BOOT0: R9.1, U10.19 (PH3)
DIV_EN: U10.2 (PB4); also elsewhere on the board
FRAM_CS: U2.1 (~CS), U10.12 (PA4); also elsewhere on the board
GND: C4.2, C5.2, C6.2, C7.2, C8.2, C9.2, C10.2, C11.2, C12.2, C13.2, C14.2, C15.2, J2.3, J3.2, R9.2, U2.4 (GND), U10.48 (VSSSMPS), U10.49 (VSS), Y1.2 (G), Y1.4 (G); also elsewhere on the board
HSE_IN: U10.26 (OSC_IN), Y1.1
HSE_OUT: U10.27 (OSC_OUT), Y1.3
I2C_SCL: U10.4 (PB6); also elsewhere on the board
I2C_SDA: U10.5 (PB7); also elsewhere on the board
LOAD_EN: U10.3 (PB5); also elsewhere on the board
LSE_IN: C14.1, U10.39 (PC14), Y2.1
LSE_OUT: C15.1, U10.40 (PC15), Y2.2
MOUNT_N: J3.1, R11.1, U10.1 (PB3)
NRST: C4.1, J2.5, R10.1, U10.18 (NRST)
PHASE: U10.16 (PA8); also elsewhere on the board
RFI_N: U10.21 (RFI_N); also elsewhere on the board
RFI_P: U10.20 (RFI_P); also elsewhere on the board
RFO_LP: U10.22 (RFO_LP); also elsewhere on the board
RF_CTRL: U10.30 (PB0); also elsewhere on the board
RF_CTRL_N: U10.32 (PB12); also elsewhere on the board
SENS_EN: U10.8 (PA1); also elsewhere on the board
SPI_MISO: U2.2 (SO), U10.14 (PA6)
SPI_MOSI: U2.5 (SI), U10.15 (PA7)
SPI_SCK: U2.6 (SCK), U10.13 (PA5)
SWCLK: J2.4, U10.42 (PA14)
SWDIO: J2.2, U10.36 (PA13)
V1V55: C10.1, C11.1, U10.25 (VDDPA), U10.29 (VDDRF1V55), U10.45 (VFBSMPS)
V3V3: C5.1, C6.1, C7.1, C8.1, C9.1, J2.1, R10.2, R11.2, R12.2, U2.3 (~WP), U2.7 (~HOLD), U2.8 (VDD), U10.11 (VDD), U10.28 (VDDRF), U10.37 (VBAT), U10.44 (VDD), U10.46 (VDDSMPS); also elsewhere on the board
VDDA: C12.1, C13.1, R12.1, U10.41 (VDDA)
VR_PA: U10.24 (VR_PA); also elsewhere on the board

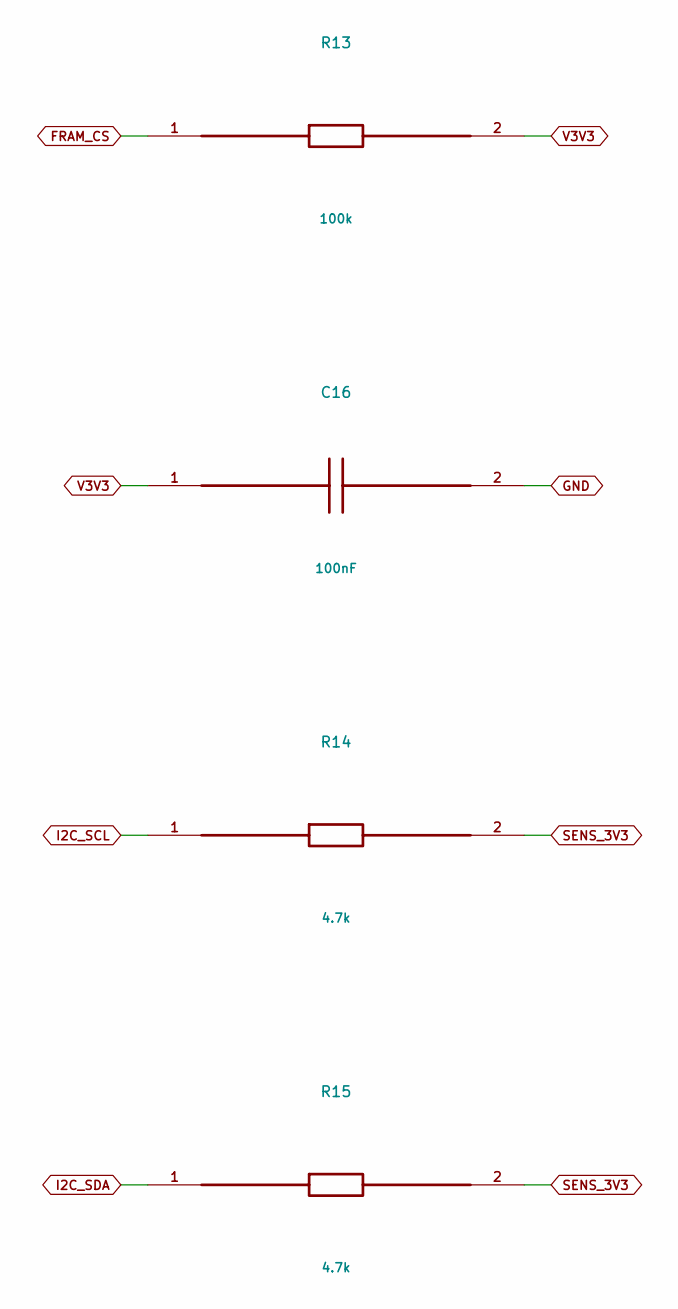
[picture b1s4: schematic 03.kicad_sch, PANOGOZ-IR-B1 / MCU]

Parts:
C16: 100nF; C_0402_1005Metric; MPN X7R 16V 100nF
R13: 100k; R_0402_1005Metric; MPN 1% thick film 100k
R14, R15: 4.7k; R_0402_1005Metric; MPN 1% thick film 4.7k

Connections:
FRAM_CS: R13.1; also elsewhere on the board
GND: C16.2; also elsewhere on the board
I2C_SCL: R14.1; also elsewhere on the board
I2C_SDA: R15.1; also elsewhere on the board
SENS_3V3: R14.2, R15.2; also elsewhere on the board
V3V3: C16.1, R13.2; also elsewhere on the board
